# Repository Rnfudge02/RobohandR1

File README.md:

# RobohandR1 Firmware

## Overview

RobohandR1 is an embedded firmware project for the Raspberry Pi Pico 2W (RP2350) microcontroller that provides a robust framework for robotics applications. The system includes a multi-core cooperative/preemptive scheduler, comprehensive statistics collection, hardware diagnostics, and sensor integration.

## Features

- **Dual-core Scheduler**: Supports both cooperative and preemptive multitasking with 5 priority levels, core affinity, and runtime statistics
- **USB Shell Interface**: Command-line interface for system interaction and debugging with command completion
- **Statistics Collection**: System-wide performance metrics including CPU usage, memory usage, and task execution timing
- **Hardware Diagnostics**: Cache and FPU status detection, benchmark capabilities, and optimization suggestions
- **IMU Integration**: Driver for ICM42670-P 6-axis IMU with DMA support and double buffering for efficient data acquisition

## Hardware Requirements

- Raspberry Pi Pico 2W (RP2350)
- ICM42670-P IMU connected via I2C
- USB connection for shell interface

## Building the Project

1. Ensure you have the Raspberry Pi Pico SDK installed and properly configured
2. Configure the CMake build system:
   ```
   mkdir build
   cd build
   cmake ..
   ```
3. Build the project:
   ```
   make
   ```
4. Flash the firmware to your Raspberry Pi Pico 2W:
   ```
   make flash
   ```

## Project Structure

```
./Include
├── Core              # Core system components
│   ├── hardware_stats.h
│   ├── hardware_stats_shell_commands.h
│   ├── mem_usage.h
│   ├── scheduler.h
│   ├── scheduler_shell_commands.h
│   ├── stats.h
│   ├── stats_shell_commands.h
│   └── usb_shell.h
└── Drivers           # Hardware device drivers
    ├── icm42670.h
    └── icm42670_shell_commands.h
    
./Src
├── Core              # Core implementations
│   ├── hardware_stats.c
│   ├── hardware_stats_shell_commands.c
│   ├── mem_usage.c
│   ├── scheduler.c
│   ├── scheduler_shell_commands.c
│   ├── stats.c
│   ├── stats_shell_commands.c
│   └── usb_shell.c
├── Drivers           # Driver implementations
│   ├── icm42670.c
│   └── icm42670_shell_commands.c
└── main.c            # Application entry point
```

## Shell Commands

The firmware provides a comprehensive set of shell commands for interacting with the system:

### Scheduler Commands
- `scheduler <start|stop|status>` - Control and monitor the scheduler
- `task create <n> <priority> <core> [type]` - Create a test task
- `ps` - List all tasks
- `stats` - Show scheduler statistics
- `trace <on|off>` - Enable/disable scheduler tracing

### System Stats Commands
- `sys_stats` - Show system performance statistics
- `task_stats` - Show task timing statistics
- `opt [suggest]` - Show/suggest optimizations
- `buffers` - Show registered buffers
- `statreset <all|tasks>` - Reset statistics

### Hardware Diagnostic Commands
- `hw_stats [status|detail|benchmark|monitor]` - View and test cache/FPU functionality

### IMU Commands
- WIP

## Extending the System

### Adding a New Command
1. Create a handler function with the signature: `int cmd_handler(int argc, char *argv[])`
2. Create a `shell_command_t` structure with your command name, help text, and handler
3. Register the command using `shell_register_command(&your_command)`

### Adding a New Driver
1. Create header (.h) and implementation (.c) files in the appropriate directories
2. Follow the driver template pattern in the existing code
3. Implement shell commands for interacting with your device
4. Register your shell commands during initialization

## Performance Considerations

The system is designed for real-time applications with these optimizations:
- Critical functions placed in RAM for faster execution
- XIP cache enabled for improved flash performance
- FPU enabled for accelerated floating-point calculations
- Multicore task distribution for parallel processing

## License

- This project is licensed under the Apache-2.0 license, which is found in the included LICENSE file.

## Contributors

- Robert Fudge (rnfudge@mun.ca)

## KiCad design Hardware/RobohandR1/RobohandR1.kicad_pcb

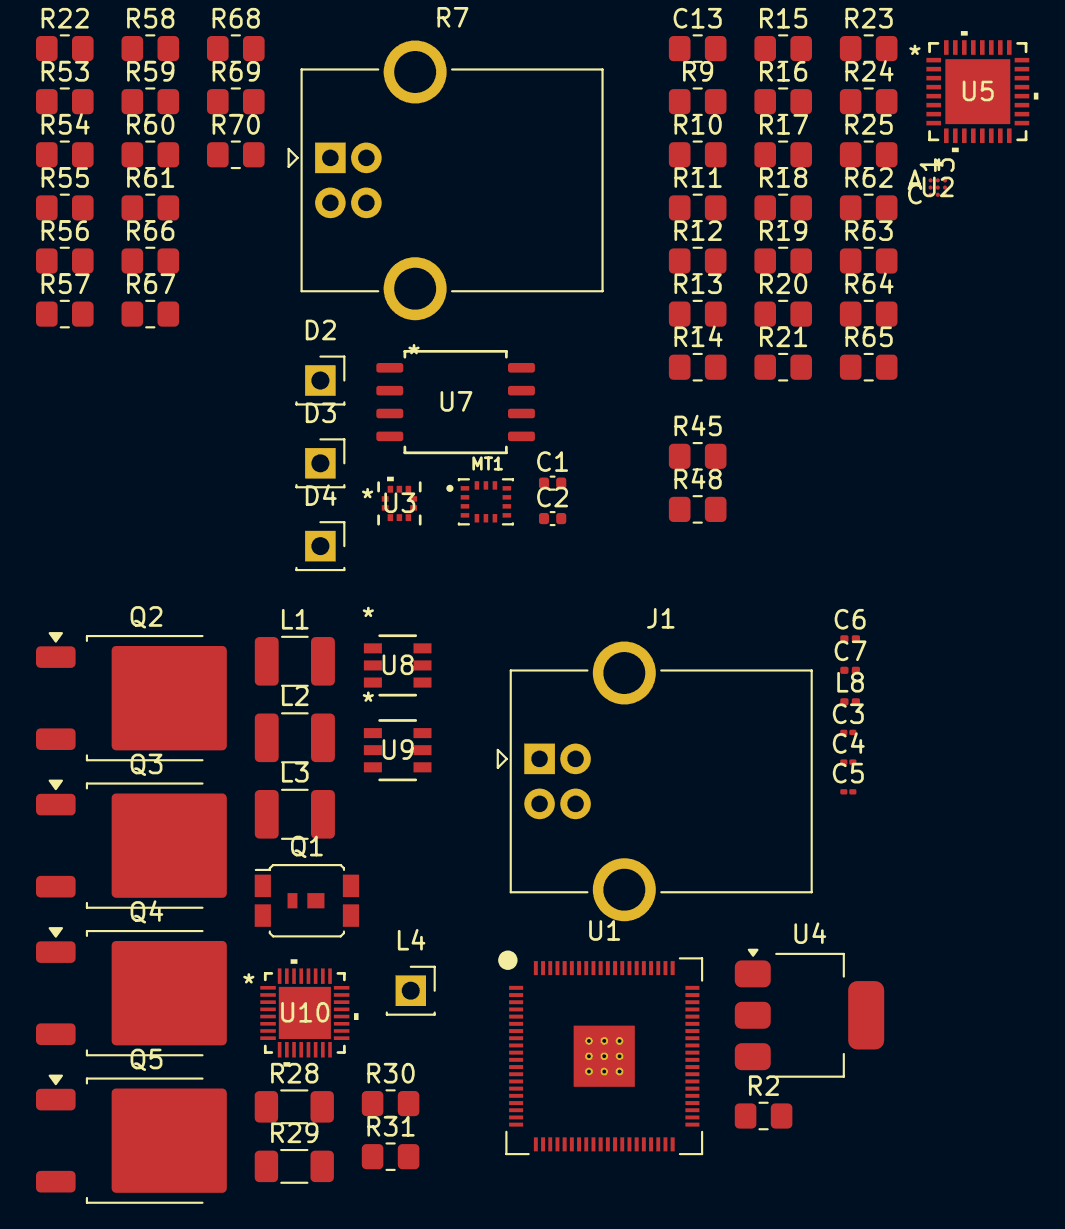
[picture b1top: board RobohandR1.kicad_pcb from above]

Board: 2 copper layers, 75 parts (0 on the bottom side), 57 nets, no tracks yet.

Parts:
C1, C2: 100nF; C_0402_1005Metric
C3, C4: 4.7uF; C_01005_0402Metric
C5: C; C_01005_0402Metric
C6, C7: 10uF; C_0201_0603Metric
C13: 1uF; R_0805_2012Metric_Pad1.20x1.40mm_HandSolder
D2: LED_R; PinSocket_1x01_P2.54mm_Vertical
D3: LED_G; PinSocket_1x01_P2.54mm_Vertical
D4: LED_B; PinSocket_1x01_P2.54mm_Vertical
J1: USB_B_Micro; USB_B_OST_USB-B1HSxx_Horizontal
L1, L2, L3: 330uH, Blocking; C_1210_3225Metric_Pad1.33x2.70mm_HandSolder
L4: 2uH; PinSocket_1x01_P2.54mm_Vertical
L8: 3.3uH; L_0201_0603Metric
MT1: ICM-42670-P; XDCR_ICM-42670-P
Q1: BSF030NE2LQ; DirectFET_SQ
Q2, Q3, Q4, Q5: QM6006D; TO-252-2
R2: 33R; R_0805_2012Metric_Pad1.20x1.40mm_HandSolder
R7: 330R; USB_B_OST_USB-B1HSxx_Horizontal
R9, R10, R11, R12, R13, R14, R15, R16, R17, R18, R19, R20, R21, R23, R24, R25: 10K; R_0805_2012Metric_Pad1.20x1.40mm_HandSolder
R22: 330R; R_0805_2012Metric_Pad1.20x1.40mm_HandSolder
R28: 24.9K, 1%; R_1206_3216Metric_Pad1.30x1.75mm_HandSolder
R29: 100K, 1%; R_1206_3216Metric_Pad1.30x1.75mm_HandSolder
R30, R31: 100K; R_0805_2012Metric_Pad1.20x1.40mm_HandSolder
R45: 1R; R_0805_2012Metric_Pad1.20x1.40mm_HandSolder
R48: 100R; R_0805_2012Metric_Pad1.20x1.40mm_HandSolder
R53, R58, R63, R65, R70: 4.7K; R_0805_2012Metric_Pad1.20x1.40mm_HandSolder
R54, R55, R56, R57, R60, R61, R64, R68, R69: 10R; R_0805_2012Metric_Pad1.20x1.40mm_HandSolder
R59, R62, R66, R67: 0R; R_0805_2012Metric_Pad1.20x1.40mm_HandSolder
U1: RP2350B-QFN80; RP2350B_QFN-80_EP_10.573x10.573_Pitch0.4mm
U2: BMM350; BGA9_BMM350_BOS-M
U3: BMP390; 10LGA_2X2X0p75_BOS-M
U4: NCP1117-1.5_SOT223; SOT-223-3_TabPin2
U5: AD7490WBCSZ; CS-32-3_ADI
U7: W25Q16JVSSIQ; W25Q16JVSSIQ_WIN
U8, U9: LMR51430XDDCR; SOT-23-THIN-6_DDC_TEX
U10: BQ25723RSNR; WQFN32_BQ25723_TEX-M

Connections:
/Analog Side/3V3: R65.2, U2.B3 (VDDIO), U2.C1 (VDD)
/Analog Side/AGND: U5.12 (AGND), U5.19 (AGND), U5.22 (AGND)
/Analog Side/IND_1-: R9.1, U5.26 (VIN14)
/Analog Side/IND_2-: R10.1, U5.27 (VIN13)
/Analog Side/IND_3-: R11.1, U5.28 (VIN12)
/Analog Side/MDL_1-: R25.1, U5.9 (VIN2)
/Analog Side/MDL_2-: R24.1, U5.10 (VIN1)
/Analog Side/MDL_3-: R23.1, U5.11 (VIN0)
/Analog Side/PKY_1-: R12.1, U5.29 (VIN11)
/Analog Side/PKY_2-: R15.1, U5.30 (VIN10)
/Analog Side/PKY_3-: R14.1, U5.31 (VIN9)
/Analog Side/PLM_1: R21.2, U5.2 (VIN8)
/Analog Side/PLM_2: R13.1, U5.24 (VIN15)
/Analog Side/RNG_1-: R18.2, U5.5 (VIN5)
/Analog Side/RNG_2-: R17.2, U5.6 (VIN4)
/Analog Side/RNG_3-: R16.2, U5.7 (VIN3)
/Analog Side/TMB_1-: R20.2, U5.3 (VIN7)
/Analog Side/TMB_2-: R19.2, U5.4 (VIN6)
/Digital Side/1V1: C3.1, L8.1, U1.65 (VREG_FB)
/Digital Side/3V3: C4.1, R2.1, U1.64 (VREG_VIN)
/Digital Side/3V3_USB: C7.1, U4.2 (VO)
/Digital Side/5V0_USB: C6.1, J1.1 (VBUS), U4.3 (VI)
/Digital Side/Sensors/3V3: C1.1, C2.1, MT1.2 (RESV), MT1.3 (RESV__1), MT1.5 (VDDIO), MT1.8 (VDD), MT1.10 (RESV__2), MT1.11 (RESV__3), MT1.12 (AP_CS), R53.2, R58.2, R70.2, U3.1 (VDDIO), U3.10 (VDD), U7.8
/Digital Side/Sensors/QSPI_CS: R53.1, U7.1
/Digital Side/Sensors/SPI1_CS1: R70.1, U3.6 (CSB)
/Digital Side/Sensors/SPI1_SCK: R59.1, R67.1
/Power Management/5V0: L2.1, R31.1, U9.3 (VIN)
/Power Management/12V0: R30.1, U8.3 (VIN)
GND: C1.2, C2.2, C3.2, C4.2, C5.2, C6.2, C7.2, C13.1, D2.1 (K), D3.1 (K), D4.1 (K), J1.5 (GND), L1.1, MT1.6 (GND), MT1.7 (FSYNC), R7.2, R22.2, R29.2, U1.62 (VREG_PGND), U1.81 (GND), U2.B1 (GND), U2.B2 (ADSEL), U2.C3 (BYPASS), U3.3 (VSS), U3.8 (VSS), U3.9 (VSS), U4.1 (GND), U7.4, U8.1 (GND), U9.1 (GND), U10.33 (EPAD)
unnamed: L1.2, L3.1
unnamed: R28.2, R29.1
unnamed: J1.3 (D+), U1.66 (USB_DM)
unnamed: J1.2 (D-), U1.67 (USB_DP)
unnamed: MT1.13 (AP_SCL/AP_SCLK), R59.2
unnamed: MT1.14 (AP_SDA/AP_SDIO/AP_SDI), R60.2
unnamed: MT1.1 (AP_SDO/AP_AD0), R61.2
unnamed: R54.1, U7.2
unnamed: R55.1, U7.3
unnamed: R56.1, U7.5
unnamed: R57.1, U7.7
unnamed: R66.2, U7.6
unnamed: U1.10 (DVDD), U1.32 (DVDD), U1.51 (DVDD)
unnamed: U1.5 (IOVDD), U1.15 (IOVDD), U1.24 (IOVDD), U1.29 (IOVDD), U1.41 (IOVDD), U1.50 (IOVDD), U1.60 (IOVDD), U1.76 (IOVDD)
unnamed: C5.1, R2.2, U1.61 (VREG_AVDD)
unnamed: L8.2, U1.63 (VREG_LX)
unnamed: R67.2, U3.2 (SCK)
unnamed: R68.2, U3.4 (SDI)
unnamed: R69.2, U3.5 (SDO)
unnamed: R65.1, U5.18 (*CS)
unnamed: R64.1, U5.17 (DIN)
unnamed: R63.2, U5.13 (DOUT)
unnamed: C13.2, U5.33 (GND)
unnamed: R9.2, R10.2, R11.2, R12.2, R13.2, R14.2, R15.2, R16.1, R17.1, R18.1, R19.1, R20.1, R21.1, R23.2, R24.2, R25.2, U5.21 (REFIN)
unnamed: R62.2, U5.14 (SCLK)
unnamed: R30.2, U8.5 (EN)
unnamed: R28.1, U8.4 (FB)
unnamed: R31.2, U9.5 (EN)

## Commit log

2025-05-14 Stable build, adding deadlines and deadline-aware-scheduling
2025-05-21 Working to add MPU for shared memory between tasks, trustzone for privilege levels, etc.
2025-05-25 Working on fixing existing structure
2025-06-01 Development temporarily paused.
